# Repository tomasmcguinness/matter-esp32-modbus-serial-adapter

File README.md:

# Matter ESP32 Modbus Adapter
The goal of this project is to provide a simple working Modbus adapter that can expose devices over Matter. It is designed for the ESP32 MCU.

# SDM120M - Electrical Sensor

The first device supported by this project is the Eastron SDM120M Single Phase Energy Meter

The readings from this device will be exposed using as a Matter Electrical Sensor Device Type.

# Hardware - Seeed XIAO ESP32-C6

The GPIOs in code has been selected for the XIAO ESP32-C6. 

| GPIO | Connection |
|------|------------|
| 16 | MAX485 - DI   | 
| 17 | MAX485 - RO   |
| 21 | MAX485 - DE/RE|
| 22 | OLED - SDA |
| 23 | OLED - SCL |
| 2  | OLED - RESET |

Ensure there is a 120kΩ across PINS A&B of the MAX485.

The RESET net label refers to the OLED display. I couldn't find a Fritzing symbol for it.

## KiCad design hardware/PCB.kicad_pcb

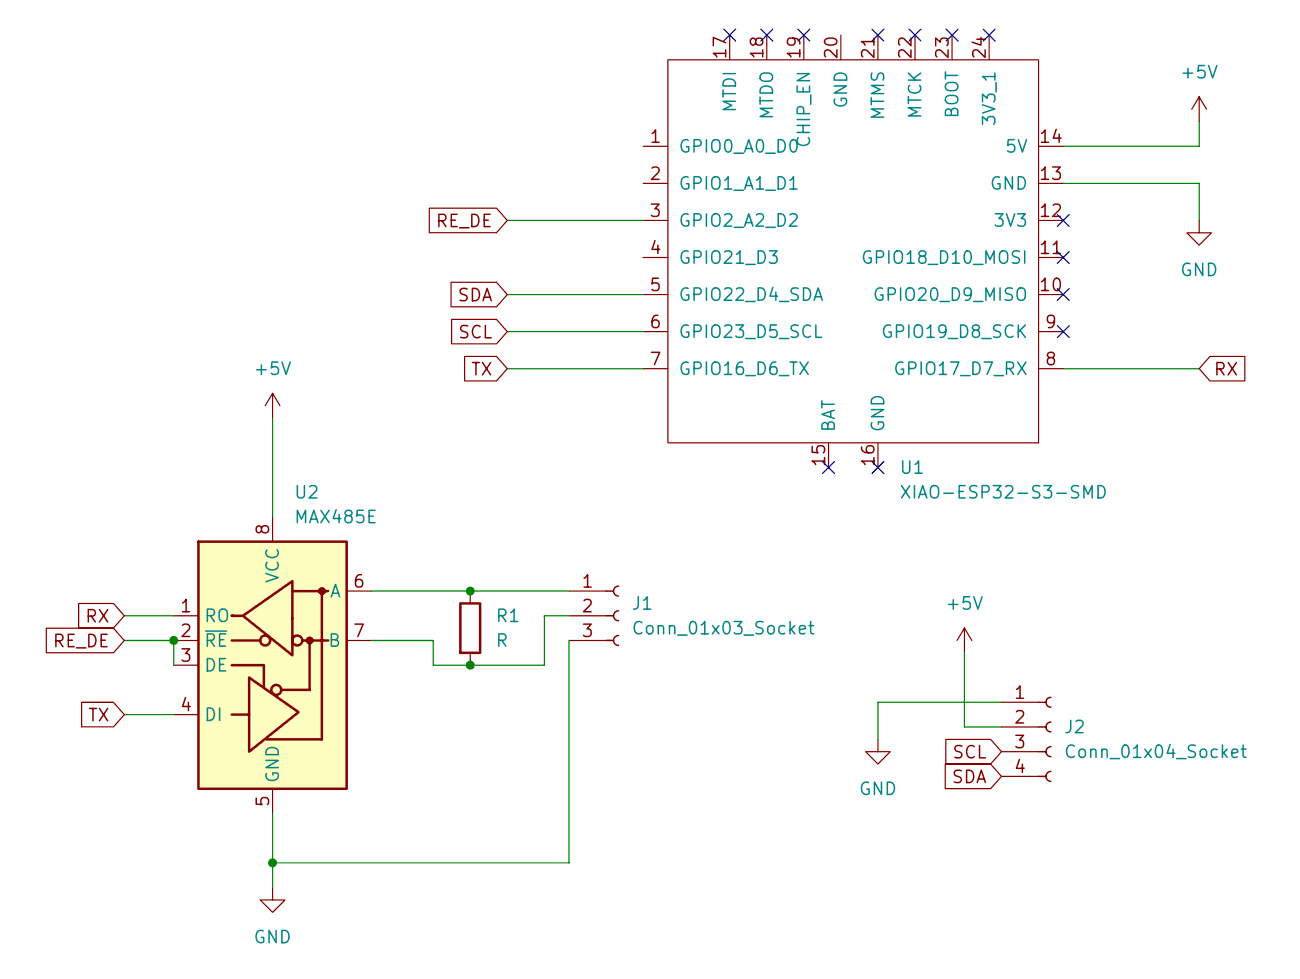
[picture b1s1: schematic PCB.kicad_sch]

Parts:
J1: Conn_01x03_Socket; PhoenixContact_SPT_1.5_3-H-3.5_1x03_P3.5mm_Horizontal
J2: Conn_01x04_Socket; PinHeader_1x04_P2.54mm_Vertical
R1: R; R_0805_2012Metric
U1: XIAO-ESP32-S3-SMD; XIAO-ESP32C6-SMD
U2: MAX485E; SOIC-8_3.9x4.9mm_P1.27mm

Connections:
+5V: J2.2, U1.14 (5V), U2.8 (VCC)
GND: J1.3, J2.1, U1.13 (GND), U2.5 (GND)
unnamed: J1.1, R1.1, U2.6 (A)
unnamed: J1.2, R1.2, U2.7 (B)
RE_DE: U1.3 (GPIO2_A2_D2), U2.2 (~RE), U2.3 (DE)
RX: U1.8 (GPIO17_D7_RX), U2.1 (RO)
SCL: J2.3, U1.6 (GPIO23_D5_SCL)
SDA: J2.4, U1.5 (GPIO22_D4_SDA)
TX: U1.7 (GPIO16_D6_TX), U2.4 (DI)

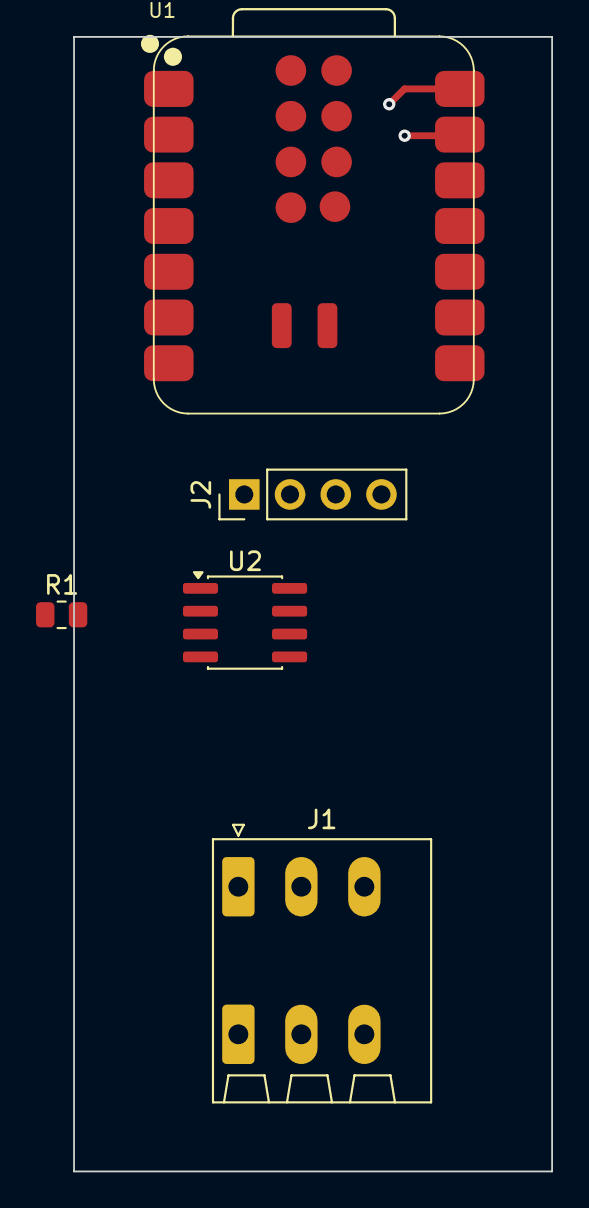
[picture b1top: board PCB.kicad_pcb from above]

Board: 2 copper layers, 26.6 x 63.0 mm, 5 parts (0 on the bottom side), 9 nets.

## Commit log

2025-08-03 Initial empty project
2026-03-20 Add project description for Matter ESP32 Modbus Adapter
2026-03-21 Initial working Modbus/MAX485
2026-03-27 Add Matter support. Refactor to split out the SDM read. Add partitions.csv
2026-03-27 Add UI to show the four readings
2026-03-28 Enable LV qr code
2026-03-28 QR Code is showing correctly.
2026-03-29 Add ElectricalPowerMeasurementDelegate implementation.
2026-03-29 Fix C -> CPP changes. Tweak readme.
2026-03-30 Move code into a firmware folder
2026-03-30 Push PIN connections
2026-03-30 Schematic updated
2026-04-01 Simple WebUSB support
2026-04-01 Two PCB tweaks
2026-04-01 PCB Backup
2026-04-02 Restore code. Add npm package files.
